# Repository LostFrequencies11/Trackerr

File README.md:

# Trackerr
 A project to make a tracking device with rudr and vari
 The tracking device that we are making for pet owner as well as a forest department officer(tracker).
 we are using GPS and LoRa to get and tranfer location Tx to Rx. currently there is a switch that we can switch between two modes but in 
 future...

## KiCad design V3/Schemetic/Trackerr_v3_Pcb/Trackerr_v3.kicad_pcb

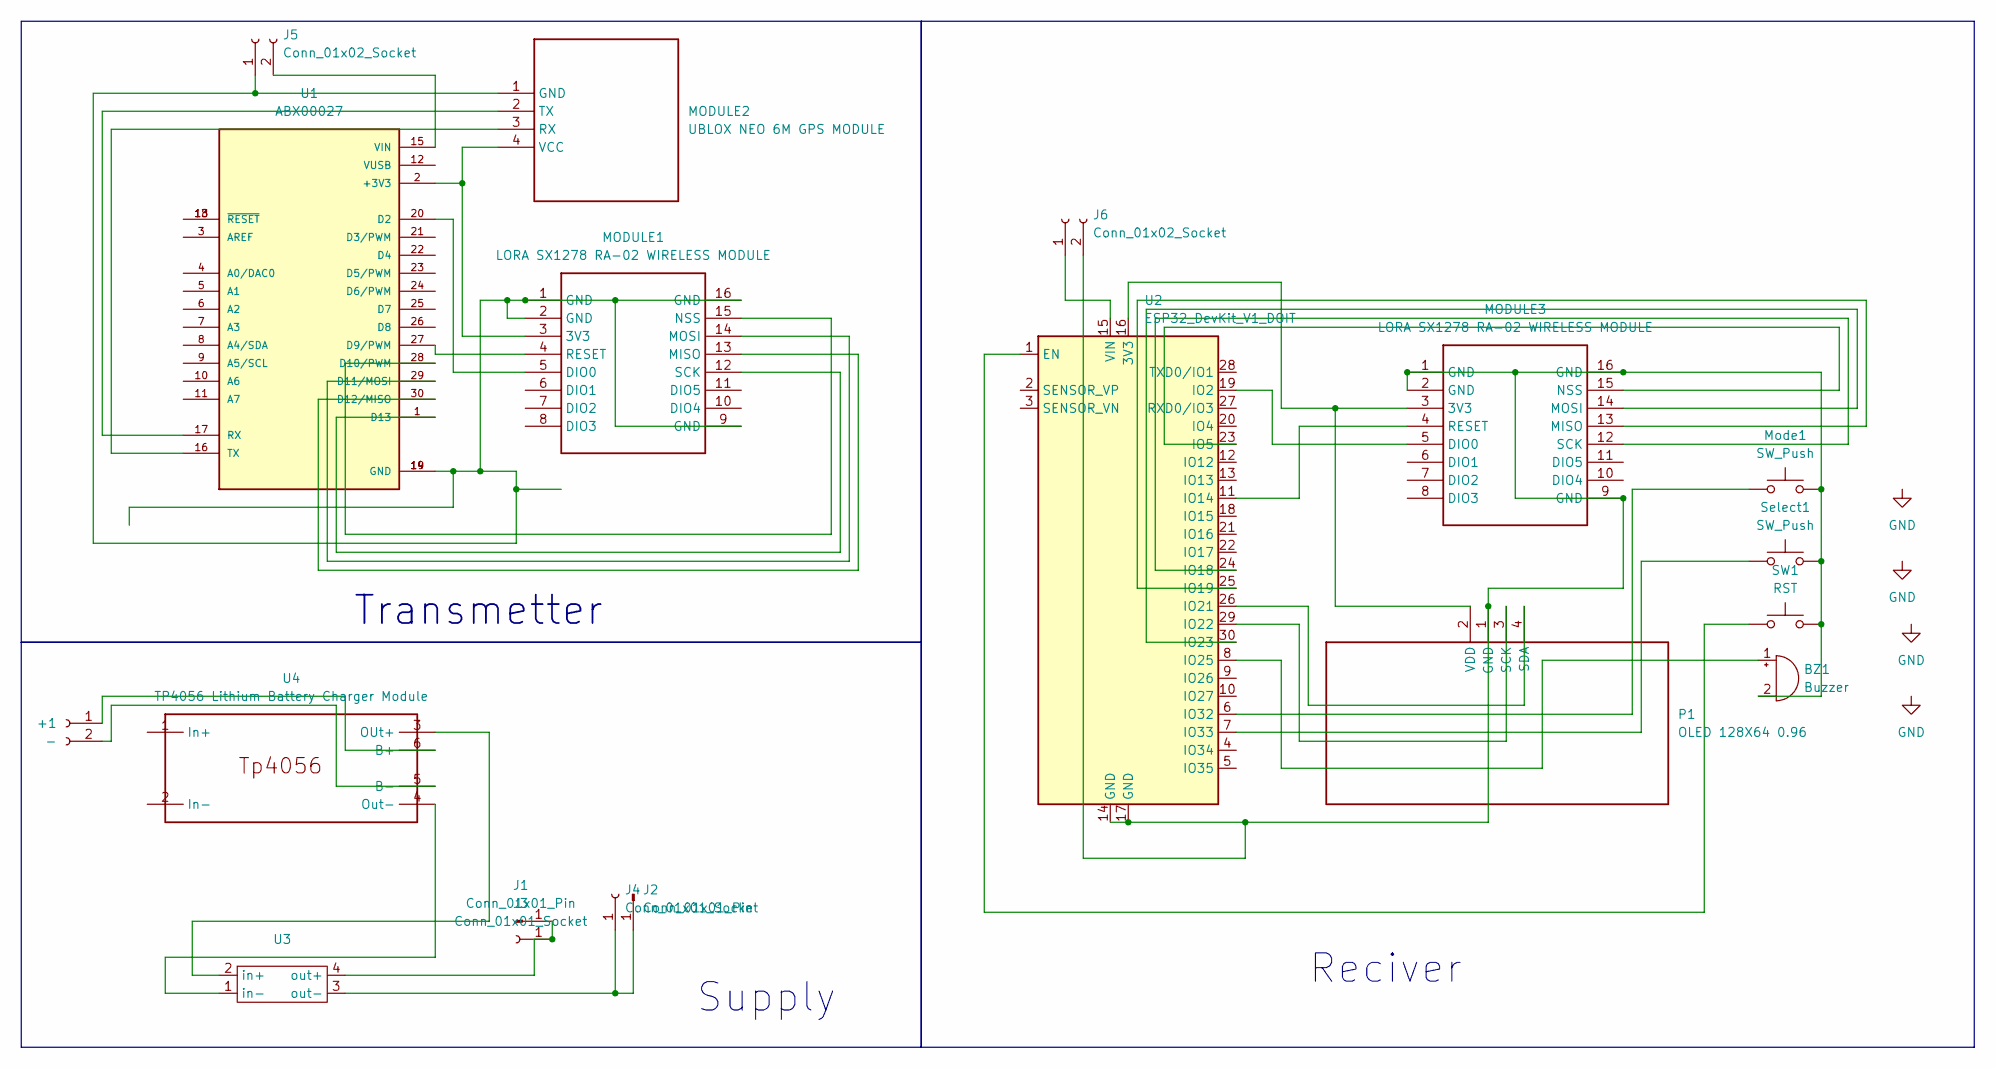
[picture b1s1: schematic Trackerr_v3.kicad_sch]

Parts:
+1: -; PinHeader_1x02_P2.54mm_Vertical
BZ1: Buzzer; Buzzer_12x9.5RM7.6
J1, J2: Conn_01x01_Pin; PinHeader_1x01_P2.54mm_Vertical
J3, J4: Conn_01x01_Socket; PinSocket_1x01_P2.54mm_Vertical
J5, J6: Conn_01x02_Socket; PinSocket_1x02_P2.54mm_Vertical
MODULE1, MODULE3: LORA SX1278 RA-02 WIRELESS MODULE
MODULE2: UBLOX NEO 6M GPS MODULE
Mode1: SW_Push; SW_1825910-6-4
P1: OLED 128X64 0.96; 0.96 AND 1.3 I2C OLED SSD1306
SW1: RST; SW_1825910-6-4
Select1: SW_Push; SW_1825910-6-4
U1: ABX00027; MODULE_ABX00027
U2: ESP32_DevKit_V1_DOIT; esp32_devkit_v1_doit
U3: LM2596 DC TO DC BUCK CONVERTER FOOTPRINT
U4: TP4056 Lithium Battery Charger Module; BATTMODULE; Manufacturer Part TP4056 Lithium Battery Charger Module

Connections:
unnamed: +1.1, U4.6 (B+)
unnamed: +1.2, U4.5 (B-)
unnamed: BZ1.1 (+), U2.8 (IO25)
unnamed: BZ1.2 (-), J6.2, MODULE3.1 (GND), MODULE3.2 (GND), MODULE3.9 (GND), MODULE3.16 (GND), Mode1.2, P1.1 (GND), SW1.2, Select1.2, U2.14 (GND), U2.17 (GND)
unnamed: J1.1, J3.1, U3.4 (out+)
unnamed: J2.1, J4.1, U3.3 (out-)
unnamed 6: J5.1, MODULE1.1 (GND), MODULE1.2 (GND), MODULE1.9 (GND), MODULE1.16 (GND), MODULE2.1 (GND), U1.14 (GND), U1.19 (GND); also elsewhere on the board
unnamed: J5.2, U1.15 (VIN)
unnamed: J6.1, U2.15 (VIN)
unnamed 9: MODULE1.3 (3V3), MODULE2.4 (VCC), U1.2 (+3V3); also elsewhere on the board
unnamed 10: MODULE1.5 (DIO0), U1.20 (D2); also elsewhere on the board
unnamed 11: MODULE1.13 (MISO), U1.30 (D12/MISO); also elsewhere on the board
unnamed 12: MODULE1.14 (MOSI), U1.29 (D11/MOSI); also elsewhere on the board
unnamed 13: MODULE1.15 (NSS), U1.28 (D10/PWM); also elsewhere on the board
unnamed 14: MODULE1.4 (RESET), U1.27 (D9/PWM); also elsewhere on the board
unnamed 15: MODULE1.12 (SCK), U1.1 (D13); also elsewhere on the board
unnamed: MODULE2.3 (RX), U1.16 (TX)
unnamed: MODULE2.2 (TX), U1.17 (RX)
unnamed: MODULE3.3 (3V3), P1.2 (VDD), U2.16 (3V3)
unnamed: MODULE3.5 (DIO0), U2.19 (IO2)
unnamed: MODULE3.13 (MISO), U2.25 (IO19)
unnamed: MODULE3.14 (MOSI), U2.30 (IO23)
unnamed: MODULE3.15 (NSS), U2.23 (IO5)
unnamed: MODULE3.4 (RESET), U2.11 (IO14)
unnamed: MODULE3.12 (SCK), U2.24 (IO18)
unnamed: P1.3 (SCK), U2.29 (IO22)
unnamed: P1.4 (SDA), U2.26 (IO21)
unnamed: U1.13 (~RESET), U1.18 (~RESET)
unnamed: SW1.1, U2.1 (EN)
unnamed: Mode1.1, U2.6 (IO32)
unnamed: Select1.1, U2.7 (IO33)
unnamed: U3.2 (in+), U4.3 (OUt+)
unnamed: U3.1 (in-), U4.4 (Out-)

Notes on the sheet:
Supply
Transmetter
Reciver

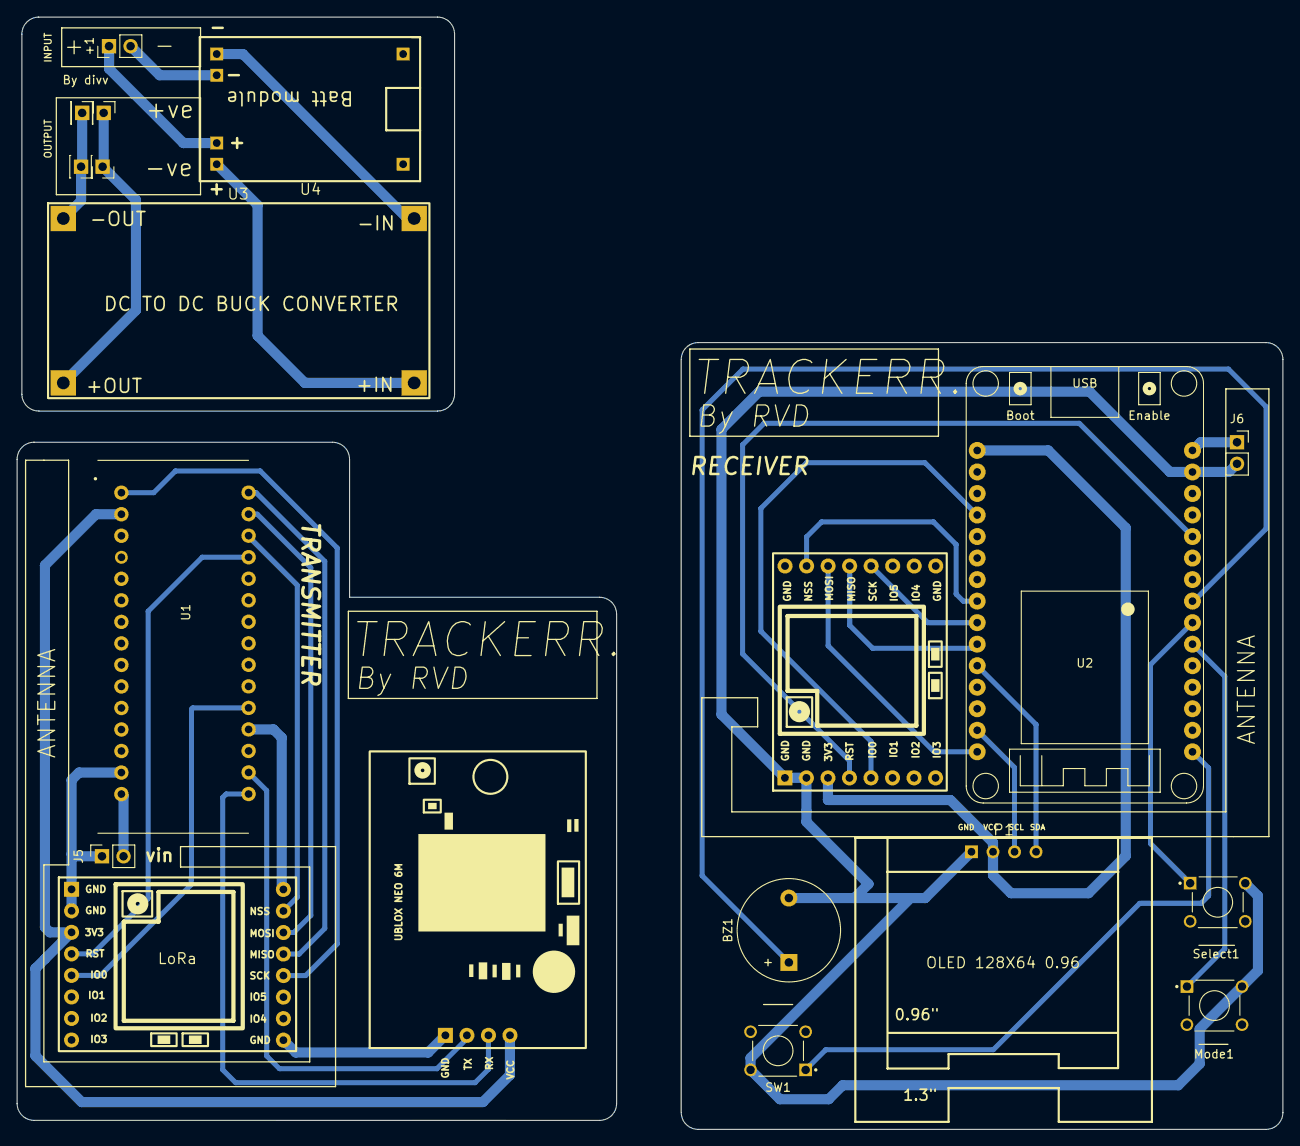
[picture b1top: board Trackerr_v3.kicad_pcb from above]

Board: 2 copper layers, 149.4 x 131.2 mm, 19 parts (0 on the bottom side), 33 nets.

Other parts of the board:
LoRa: LORA SX1278 RA-02 WIRELESS MODULE

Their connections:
unnamed 6: LoRa.1 (GND), LoRa.2 (GND), LoRa.9 (GND), LoRa.16 (GND); also elsewhere on the board
unnamed 9: LoRa.3 (3V3); also elsewhere on the board
unnamed 10: LoRa.5 (DIO0); also elsewhere on the board
unnamed 11: LoRa.13 (MISO); also elsewhere on the board
unnamed 12: LoRa.14 (MOSI); also elsewhere on the board
unnamed 13: LoRa.15 (NSS); also elsewhere on the board
unnamed 14: LoRa.4 (RESET); also elsewhere on the board
unnamed 15: LoRa.12 (SCK); also elsewhere on the board

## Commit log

2025-02-07 Create V3
2025-02-07 Update FIle
2025-02-17 Edit
